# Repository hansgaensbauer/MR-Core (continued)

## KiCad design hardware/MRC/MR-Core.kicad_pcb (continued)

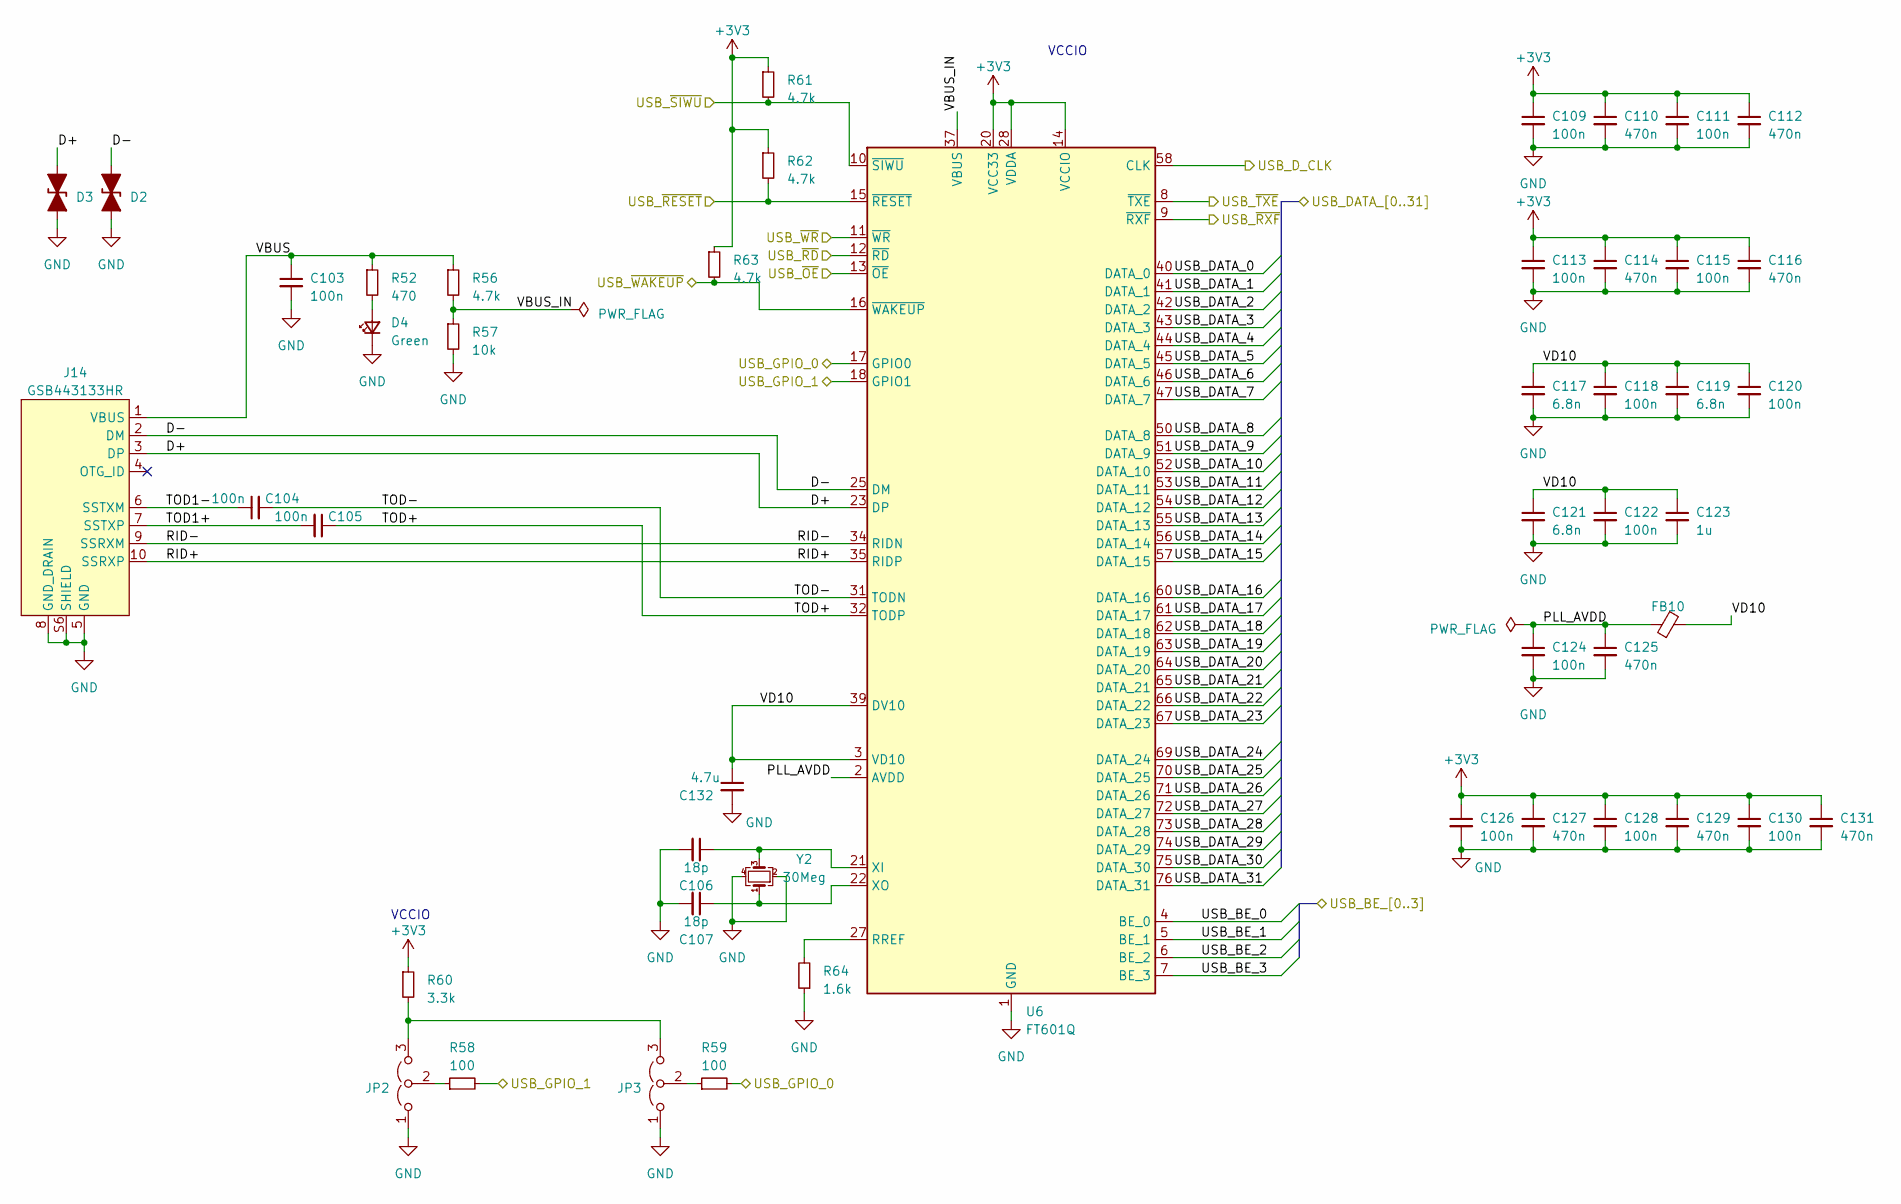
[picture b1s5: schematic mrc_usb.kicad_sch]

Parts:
C103, C104, C105, C109, C111, C113, C115, C118, C120, C122, C124, C126, C128, C130: 100n; C_0603_1608Metric; MPN C14663
C106, C107: 18p; C_0603_1608Metric; MPN C1647
C110, C112, C114, C116, C125, C127, C129, C131: 470n; C_0603_1608Metric; MPN C1623
C117, C119, C121: 6.8n; C_0603_1608Metric; MPN C1631
C123: 1u; C_0603_1608Metric; MPN C15849
C132: 4.7u; C_0603_1608Metric; MPN C19666
D2, D3: D_TVS_Filled; D_SOD-123
D4: Green; LED_0603_1608Metric; MPN C2290
FB10: FerriteBead_Small; L_0603_1608Metric; MPN C14709
J14: GSB443133HR; AMPHENOL_GSB443133HR; MPN C5428289(need to confirm)
JP2, JP3: Jumper_3_Open; SolderJumper-3_P1.3mm_Open_Pad1.0x1.5mm
R52: 470; R_0603_1608Metric; MPN C23179
R56, R61, R62, R63: 4.7k; R_0603_1608Metric; MPN C23162
R57: 10k; R_0603_1608Metric; MPN C25804
R58, R59: 100; R_0603_1608Metric; MPN C22775
R60: 3.3k; R_0603_1608Metric; MPN C22978
R64: 1.6k; R_0603_1608Metric; MPN C22847
U6: FT601Q; QFN-76-1EP_9x9mm_P0.4mm_EP5.81x6.31mm; MPN C1550513
Y2: 30Meg; Crystal_SMD_3225-4Pin_3.2x2.5mm; MPN C20885054

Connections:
+3V3: C109.1, C110.1, C111.1, C112.1, C113.1, C114.1, C115.1, C116.1, C126.1, C127.1, C128.1, C129.1, C130.1, C131.1, R60.1, R61.1, R62.1, R63.1, U6.14 (VCCIO), U6.20 (VCC33), U6.24 (VCC33), U6.28 (VDDA), U6.38 (VCC33), U6.49 (VCCIO), U6.59 (VCCIO), U6.68 (VCCIO); also elsewhere on the board
/Artix-7/USB_BE_0: U6.4 (BE_0); also elsewhere on the board
/Artix-7/USB_BE_1: U6.5 (BE_1); also elsewhere on the board
/Artix-7/USB_BE_2: U6.6 (BE_2); also elsewhere on the board
/Artix-7/USB_BE_3: U6.7 (BE_3); also elsewhere on the board
/Artix-7/USB_DATA_0: U6.40 (DATA_0); also elsewhere on the board
/Artix-7/USB_DATA_1: U6.41 (DATA_1); also elsewhere on the board
/Artix-7/USB_DATA_2: U6.42 (DATA_2); also elsewhere on the board
/Artix-7/USB_DATA_3: U6.43 (DATA_3); also elsewhere on the board
/Artix-7/USB_DATA_4: U6.44 (DATA_4); also elsewhere on the board
/Artix-7/USB_DATA_5: U6.45 (DATA_5); also elsewhere on the board
/Artix-7/USB_DATA_6: U6.46 (DATA_6); also elsewhere on the board
/Artix-7/USB_DATA_7: U6.47 (DATA_7); also elsewhere on the board
/Artix-7/USB_DATA_8: U6.50 (DATA_8); also elsewhere on the board
/Artix-7/USB_DATA_9: U6.51 (DATA_9); also elsewhere on the board
/Artix-7/USB_DATA_10: U6.52 (DATA_10); also elsewhere on the board
/Artix-7/USB_DATA_11: U6.53 (DATA_11); also elsewhere on the board
/Artix-7/USB_DATA_12: U6.54 (DATA_12); also elsewhere on the board
/Artix-7/USB_DATA_13: U6.55 (DATA_13); also elsewhere on the board
/Artix-7/USB_DATA_14: U6.56 (DATA_14); also elsewhere on the board
/Artix-7/USB_DATA_15: U6.57 (DATA_15); also elsewhere on the board
/Artix-7/USB_DATA_16: U6.60 (DATA_16); also elsewhere on the board
/Artix-7/USB_DATA_17: U6.61 (DATA_17); also elsewhere on the board
/Artix-7/USB_DATA_18: U6.62 (DATA_18); also elsewhere on the board
/Artix-7/USB_DATA_19: U6.63 (DATA_19); also elsewhere on the board
/Artix-7/USB_DATA_20: U6.64 (DATA_20); also elsewhere on the board
/Artix-7/USB_DATA_21: U6.65 (DATA_21); also elsewhere on the board
/Artix-7/USB_DATA_22: U6.66 (DATA_22); also elsewhere on the board
/Artix-7/USB_DATA_23: U6.67 (DATA_23); also elsewhere on the board
/Artix-7/USB_DATA_24: U6.69 (DATA_24); also elsewhere on the board
/Artix-7/USB_DATA_25: U6.70 (DATA_25); also elsewhere on the board
/Artix-7/USB_DATA_26: U6.71 (DATA_26); also elsewhere on the board
/Artix-7/USB_DATA_27: U6.72 (DATA_27); also elsewhere on the board
/Artix-7/USB_DATA_28: U6.73 (DATA_28); also elsewhere on the board
/Artix-7/USB_DATA_29: U6.74 (DATA_29); also elsewhere on the board
/Artix-7/USB_DATA_30: U6.75 (DATA_30); also elsewhere on the board
/Artix-7/USB_DATA_31: U6.76 (DATA_31); also elsewhere on the board
/Artix-7/USB_D_CLK: U6.58 (CLK); also elsewhere on the board
/Artix-7/USB_GPIO_0: R59.2, U6.17 (GPIO0); also elsewhere on the board
/Artix-7/USB_GPIO_1: R58.2, U6.18 (GPIO1); also elsewhere on the board
/Artix-7/USB_~OE: U6.13 (~OE); also elsewhere on the board
/Artix-7/USB_~RD: U6.12 (~RD); also elsewhere on the board
/Artix-7/USB_~RESET: R62.2, U6.15 (~RESET); also elsewhere on the board
/Artix-7/USB_~RXF: U6.9 (~RXF); also elsewhere on the board
/Artix-7/USB_~SIWU: R61.2, U6.10 (~SIWU); also elsewhere on the board
/Artix-7/USB_~TXE: U6.8 (~TXE); also elsewhere on the board
/Artix-7/USB_~WAKEUP: R63.2, U6.16 (~WAKEUP); also elsewhere on the board
/Artix-7/USB_~WR: U6.11 (~WR); also elsewhere on the board
/USB-FIFO/D+: D3.2 (A2), J14.3 (DP), U6.23 (DP)
/USB-FIFO/D-: D2.2 (A2), J14.2 (DM), U6.25 (DM)
/USB-FIFO/PLL_AVDD: C124.1, C125.1, FB10.1, U6.2 (AVDD)
/USB-FIFO/RID+: J14.10 (SSRXP), U6.35 (RIDP)
/USB-FIFO/RID-: J14.9 (SSRXM), U6.34 (RIDN)
/USB-FIFO/TOD1+: C105.2, J14.7 (SSTXP)
/USB-FIFO/TOD1-: C104.1, J14.6 (SSTXM)
/USB-FIFO/TOD+: C105.1, U6.32 (TODP)
/USB-FIFO/TOD-: C104.2, U6.31 (TODN)
/USB-FIFO/VBUS: C103.1, J14.1 (VBUS), R52.1, R56.1
/USB-FIFO/VBUS_IN: R56.2, R57.1, U6.37 (VBUS)
/USB-FIFO/VD10: C117.1, C118.1, C119.1, C120.1, C121.1, C122.1, C123.1, C132.1, FB10.2, U6.3 (VD10), U6.30 (VD10), U6.33 (VD10), U6.39 (DV10), U6.48 (VD10)
unnamed: D4.2 (A), R52.2
unnamed: JP2.3 (B), JP3.3 (B), R60.2
unnamed: JP2.2 (C), R58.1
unnamed: JP3.2 (C), R59.1
unnamed: R64.2, U6.27 (RREF)
unnamed: C106.1, U6.21 (XI), Y2.3
unnamed: C107.1, U6.22 (XO), Y2.1

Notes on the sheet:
VCCIO

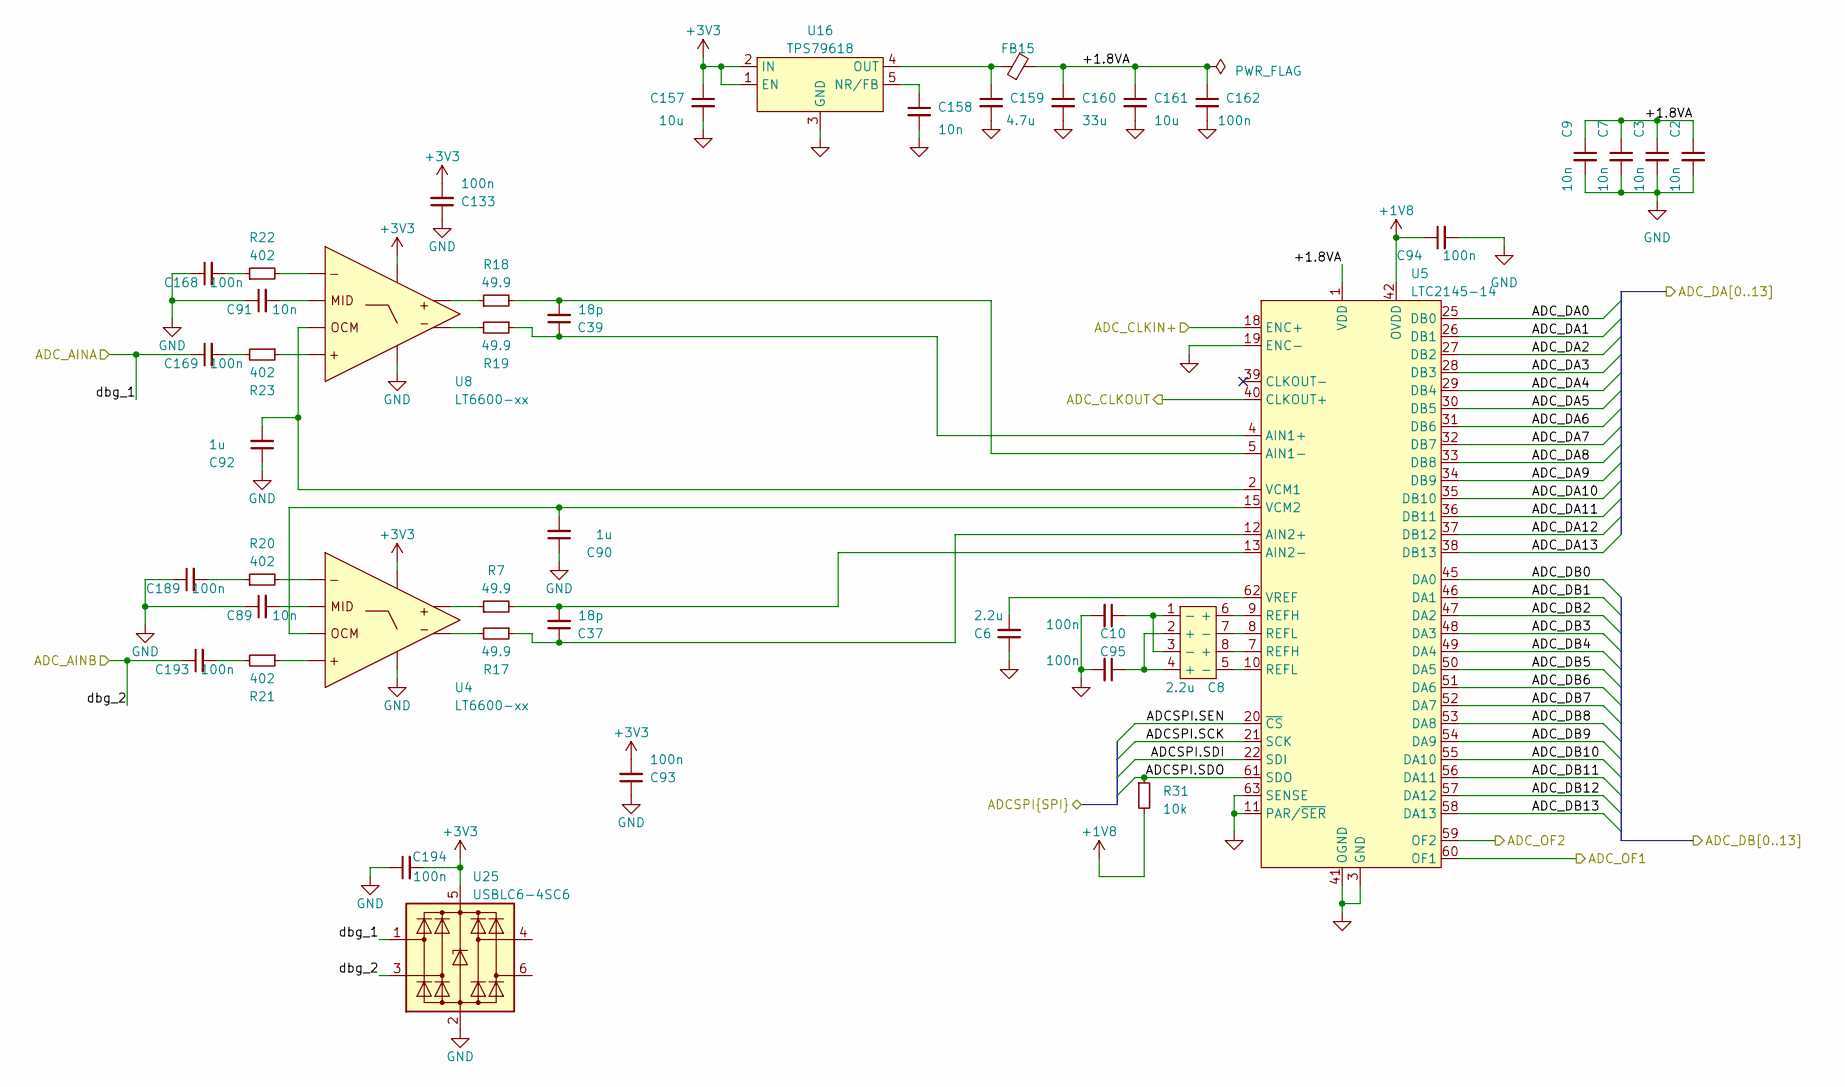
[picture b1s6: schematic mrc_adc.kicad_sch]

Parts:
C2, C3, C7, C9, C89, C91, C158: 10n; C_0603_1608Metric; MPN C57112
C6: 2.2u; C_0603_1608Metric; MPN C23630
C8: 2.2u; 0508_C_INTERDIGITATED; MPN C23630
C10, C93, C94, C95, C133, C162: 100n; C_0603_1608Metric; MPN C14663
C37, C39: 18p; C_0603_1608Metric; MPN C1647
C90, C92: 1u; C_0603_1608Metric; MPN C15849
C157, C161: 10u; C_0603_1608Metric; MPN C96446
C159: 4.7u; C_0603_1608Metric; MPN C19666
C160: 33u; C_0603_1608Metric; MPN C4978585
C168, C169, C189, C193, C194: 100n; C_0603_1608Metric; MPN C57112
FB15: FerriteBead_Small; L_0603_1608Metric; MPN C14709
R7, R17, R18, R19: 49.9; R_0603_1608Metric; MPN C23185
R20, R21, R22, R23: 402; R_0603_1608Metric; MPN C23049
R31: 10k; R_0603_1608Metric; MPN C25804
U4, U8: LT6600-xx; SO-8_3.9x4.9mm_P1.27mm; MPN C673220/C107980/C673198/C673202/C673216
U5: LTC2145-14; QFN-64-1EP_9x9mm_P0.5mm_EP7.15x7.15mm; MPN C679368/C679372
U16: TPS79618; SOT-223-6; MPN C2867020
U25: USBLC6-4SC6; SOT-23-6; MPN C5197386

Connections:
+1V8: C94.1, R31.2, U5.42 (OVDD); also elsewhere on the board
+3V3: C93.2, C133.2, C157.1, U4.3 (V+), U8.3 (V+), U16.1 (EN), U16.2 (IN); also elsewhere on the board
/ADC/+1.8VA: C2.1, C3.1, C7.1, C9.1, C160.1, C161.1, C162.1, FB15.2, U5.1 (VDD), U5.16 (VDD), U5.17 (VDD), U5.64 (VDD)
/ADC/ADCSPI.SCK: U5.21 (SCK); also elsewhere on the board
/ADC/ADCSPI.SDI: U5.22 (SDI); also elsewhere on the board
/ADC/ADCSPI.SDO: R31.1, U5.61 (SDO); also elsewhere on the board
/ADC/ADCSPI.SEN: U5.20 (~CS); also elsewhere on the board
/ADC/ADC_AINA: C169.2, R23.2; also elsewhere on the board
/ADC/ADC_AINB: C193.2, R21.2; also elsewhere on the board
/ADC/ADC_CLKOUT: U5.40 (CLKOUT+); also elsewhere on the board
/ADC/ADC_DA0: U5.25 (DB0); also elsewhere on the board
/ADC/ADC_DA1: U5.26 (DB1); also elsewhere on the board
/ADC/ADC_DA2: U5.27 (DB2); also elsewhere on the board
/ADC/ADC_DA3: U5.28 (DB3); also elsewhere on the board
/ADC/ADC_DA4: U5.29 (DB4); also elsewhere on the board
/ADC/ADC_DA5: U5.30 (DB5); also elsewhere on the board
/ADC/ADC_DA6: U5.31 (DB6); also elsewhere on the board
/ADC/ADC_DA7: U5.32 (DB7); also elsewhere on the board
/ADC/ADC_DA8: U5.33 (DB8); also elsewhere on the board
/ADC/ADC_DA9: U5.34 (DB9); also elsewhere on the board
/ADC/ADC_DA10: U5.35 (DB10); also elsewhere on the board
/ADC/ADC_DA11: U5.36 (DB11); also elsewhere on the board
/ADC/ADC_DA12: U5.37 (DB12); also elsewhere on the board
/ADC/ADC_DA13: U5.38 (DB13); also elsewhere on the board
/ADC/ADC_DB0: U5.45 (DA0); also elsewhere on the board
/ADC/ADC_DB1: U5.46 (DA1); also elsewhere on the board
/ADC/ADC_DB2: U5.47 (DA2); also elsewhere on the board
/ADC/ADC_DB3: U5.48 (DA3); also elsewhere on the board
/ADC/ADC_DB4: U5.49 (DA4); also elsewhere on the board
/ADC/ADC_DB5: U5.50 (DA5); also elsewhere on the board
/ADC/ADC_DB6: U5.51 (DA6); also elsewhere on the board
/ADC/ADC_DB7: U5.52 (DA7); also elsewhere on the board
/ADC/ADC_DB8: U5.53 (DA8); also elsewhere on the board
/ADC/ADC_DB9: U5.54 (DA9); also elsewhere on the board
/ADC/ADC_DB10: U5.55 (DA10); also elsewhere on the board
/ADC/ADC_DB11: U5.56 (DA11); also elsewhere on the board
/ADC/ADC_DB12: U5.57 (DA12); also elsewhere on the board
/ADC/ADC_DB13: U5.58 (DA13); also elsewhere on the board
/ADC/ADC_OF1: U5.60 (OF1); also elsewhere on the board
/ADC/ADC_OF2: U5.59 (OF2); also elsewhere on the board
/ADC_CLK+: U5.18 (ENC+); also elsewhere on the board
unnamed: C8.2 (+), C8.4 (+), C95.1
unnamed: C8.6 (+), U5.9 (REFH)
unnamed: C8.8 (+), U5.7 (REFH)
unnamed: C8.5 (-), U5.10 (REFL)
unnamed: C8.7 (-), U5.8 (REFL)
unnamed: C8.1 (-), C8.3 (-), C10.1
unnamed: C169.1, U25.1 (I/O1)
unnamed: C193.1, U25.3 (I/O2)
unnamed: R21.1, U4.8 (IN+)
unnamed: R20.2, U4.1 (IN-)
unnamed: R7.1, U4.4 (OUT+)
unnamed: R17.2, U4.5 (OUT-)
unnamed: C89.2, U4.7 (V_MID)
unnamed: C90.2, U4.2 (V_OCM), U5.15 (VCM2)
unnamed: C39.1, R19.1, U5.4 (AIN1+)
unnamed: C39.2, R18.2, U5.5 (AIN1-)
unnamed: C37.1, R17.1, U5.12 (AIN2+)
unnamed: C37.2, R7.2, U5.13 (AIN2-)
unnamed: C92.2, U5.2 (VCM1), U8.2 (V_OCM)
unnamed: C6.2, U5.62 (VREF)
unnamed: R23.1, U8.8 (IN+)
unnamed: R22.2, U8.1 (IN-)
unnamed: R18.1, U8.4 (OUT+)
unnamed: R19.2, U8.5 (OUT-)
unnamed: C91.2, U8.7 (V_MID)
unnamed: C158.1, U16.5 (NR/FB)
unnamed: C159.1, FB15.1, U16.4 (OUT)

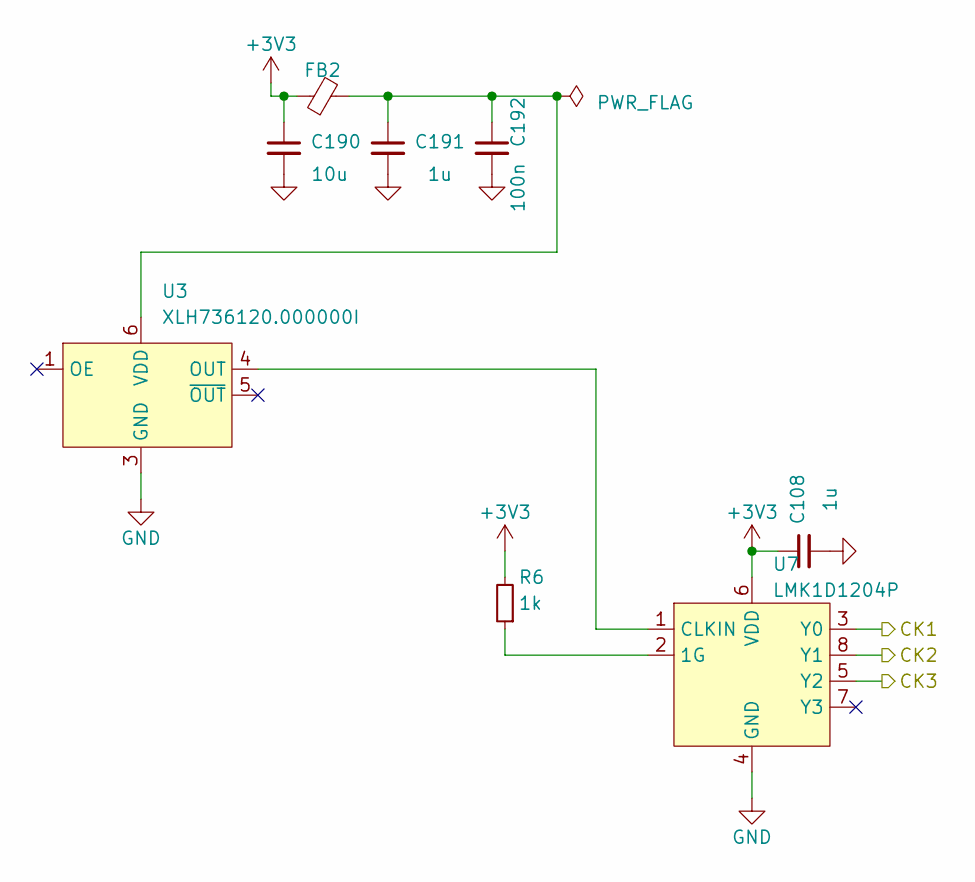
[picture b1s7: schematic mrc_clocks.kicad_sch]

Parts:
C108, C191: 1u; C_0603_1608Metric; MPN C15849
C190: 10u; C_0603_1608Metric; MPN C96446
C192: 100n; C_0603_1608Metric; MPN C14663
FB2: FerriteBead_Small; L_0603_1608Metric; MPN C14709
R6: 1k; R_0603_1608Metric; MPN C21190
U3: XLH736120.000000I; MPN C1670379
U7: LMK1D1204P; DFN-8_2x2mm_P0.5mm; MPN C3613664

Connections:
+3V3: C108.1, C190.1, FB2.1, R6.2, U7.6 (VDD); also elsewhere on the board
/ADC_CLK+: U7.3 (Y0); also elsewhere on the board
/DAC_CLK+: U7.8 (Y1); also elsewhere on the board
/FPGA_CLK+: U7.5 (Y2); also elsewhere on the board
unnamed: U3.4 (OUT), U7.1 (CLKIN)
unnamed: C191.1, C192.1, FB2.2, U3.6 (VDD)
unnamed: R6.1, U7.2 (1G)

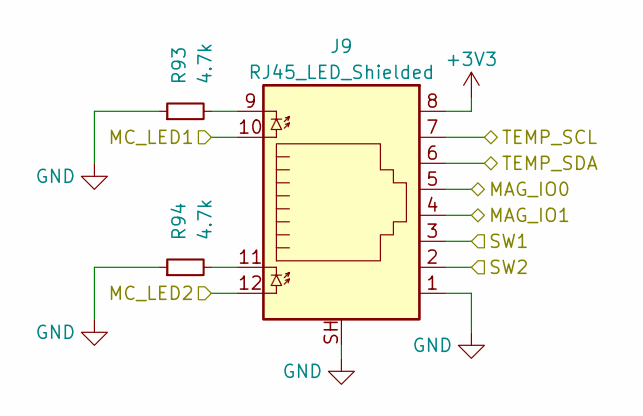
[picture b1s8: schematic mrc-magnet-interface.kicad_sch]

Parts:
J9: RJ45_LED_Shielded; RJ45_Amphenol_RJHSE538X; MPN C464586/C464587/C464588
R93, R94: 4.7k; R_0603_1608Metric; MPN C23162

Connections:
+3V3: J9.8; also elsewhere on the board
/Artix-7/SW1: J9.3; also elsewhere on the board
/Artix-7/SW2: J9.2; also elsewhere on the board
/Controller/MAG_IO0: J9.5; also elsewhere on the board
/Controller/MAG_IO1: J9.4; also elsewhere on the board
/Controller/MC_LED1: J9.10; also elsewhere on the board
/Controller/MC_LED2: J9.12; also elsewhere on the board
/Controller/TEMP_SCL: J9.7; also elsewhere on the board
/Controller/TEMP_SDA: J9.6; also elsewhere on the board
unnamed: J9.9, R93.2
unnamed: J9.11, R94.2

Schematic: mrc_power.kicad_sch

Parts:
C5, C134, C154, C197: 330n; C_0603_1608Metric; MPN C76621
C11: 4.7u; C_0603_1608Metric; MPN C19666
C135, C136, C199: 10u; C_0805_2012Metric; MPN C96446
C137, C155: 1u; C_0805_2012Metric; MPN C15849
C139, C198, C200: 47u; CP_Radial_D8.0mm_P3.50mm; MPN C318632
C170, C171: 220n; C_0603_1608Metric; MPN C21120
C201: 10u; C_1206_3216Metric; MPN C96446
D7: LED_Small; LED_0603_1608Metric; MPN C2286
J12: ASMPR45-1X2-RK; Powerpole_1x2; MPN C3683033
J19, J20, J21: Conn_01x02; JST_XH_B2B-XH-A_1x02_P2.50mm_Vertical
R1: 6.2k; R_0603_1608Metric; MPN C4260
R95: 5.62k; R_0603_1608Metric; MPN C23188
R96, R100: 3.3k; R_0603_1608Metric; MPN C22978
R97: 1k; R_0603_1608Metric; MPN C21190
R98: 2.2k; R_0603_1608Metric; MPN C4190
R99: 4.7k; R_0603_1608Metric; MPN C23162
R101: 10k; R_0603_1608Metric; MPN C25804
R102: 20k; R_0603_1608Metric; MPN C4184
TP7, TP8: TestPoint; TestPoint_THTPad_D2.0mm_Drill1.0mm
U14: LM7805_TO220; TO-220-3_BottomHeatsink; MPN C50931
U18: LM1085-12; TO-220-3_BottomHeatsink; MPN C130908
U19, U20: LD29300; P2PAK; MPN C500927
U21: MCP1827T-ADJ; P2PAK; MPN C632715(no stock)

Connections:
+1V0: C137.1, R99.1, U21.4 (OUT); also elsewhere on the board
+1V8: C136.1, R97.1, U20.4 (OUT); also elsewhere on the board
+3V3: C135.1, R95.1, U19.4 (OUT); also elsewhere on the board
+5V: C5.1, C11.1, C134.1, C139.1, C197.1, J21.1, R1.1, R101.2, R102.2, U14.3 (VO), U19.2 (IN), U20.2 (IN), U21.1 (INH), U21.2 (IN)
+12V: C198.1, C199.1, J20.1, U18.2 (VO)
+13V8: C154.1, C155.1, C200.1, C201.1, J12.1, J19.1, U14.1 (VI), U18.3 (VI); also elsewhere on the board
unnamed: D7.2 (A), R1.2
unnamed: R95.2, R96.1, U19.5 (ADJ)
unnamed: C171.2, R102.1, U19.1 (INH)
unnamed: R97.2, R98.1, U20.5 (ADJ)
unnamed: C170.2, R101.1, U20.1 (INH)
unnamed: R99.2, R100.1, U21.5 (ADJ)

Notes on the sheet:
Fan connector
LNA

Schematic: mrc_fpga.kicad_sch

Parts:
J6: Conn_02x05_Odd_Even; PinHeader_2x05_P2.54mm_Vertical
R27: 1k; R_0603_1608Metric; MPN C21190
U2: XC7A35T-FTG256; Xilinx_FTG256; MPN C9900024150

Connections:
+1V8: U2.A6 (VCCO_35), U2.B3 (VCCO_35), U2.D7 (VCCO_35), U2.E4 (VCCO_35), U2.F1 (VCCO_35), U2.J2 (VCCO_35); also elsewhere on the board
+3V3: J6.1, U2.A16 (VCCO_15), U2.B13 (VCCO_15), U2.C10 (VCCO_15), U2.E14 (VCCO_15), U2.H15 (VCCO_15), U2.J12 (VCCO_15), U2.L16 (VCCO_14), U2.M3 (VCCO_34), U2.M13 (VCCO_14), U2.N10 (VCCO_14), U2.P7 (VCCO_14), U2.R4 (VCCO_34), U2.R14 (VCCO_14), U2.T1 (VCCO_34), U2.T11 (VCCO_14); also elsewhere on the board
/ADC/ADC_CLKOUT: U2.F5 (IO_L13P_T2_MRCC_35); also elsewhere on the board
/ADC/ADC_DA0: U2.L3 (IO_L23P_T3_35); also elsewhere on the board
/ADC/ADC_DA1: U2.L2 (IO_L23N_T3_35); also elsewhere on the board
/ADC/ADC_DA2: U2.K2 (IO_L24N_T3_35); also elsewhere on the board
/ADC/ADC_DA3: U2.K3 (IO_L24P_T3_35); also elsewhere on the board
/ADC/ADC_DA4: U2.K1 (IO_L22P_T3_35); also elsewhere on the board
/ADC/ADC_DA5: U2.K5 (IO_25_35); also elsewhere on the board
/ADC/ADC_DA6: U2.J3 (IO_L21P_T3_DQS_35); also elsewhere on the board
/ADC/ADC_DA7: U2.J1 (IO_L22N_T3_35); also elsewhere on the board
/ADC/ADC_DA8: U2.J4 (IO_L19N_T3_VREF_35); also elsewhere on the board
/ADC/ADC_DA9: U2.H2 (IO_L20P_T3_35); also elsewhere on the board
/ADC/ADC_DA10: U2.J5 (IO_L19P_T3_35); also elsewhere on the board
/ADC/ADC_DA11: U2.H3 (IO_L21N_T3_DQS_35); also elsewhere on the board
/ADC/ADC_DA12: U2.G1 (IO_L17N_T2_35); also elsewhere on the board
/ADC/ADC_DA13: U2.G2 (IO_L17P_T2_35); also elsewhere on the board
/ADC/ADC_DB0: U2.H4 (IO_L18N_T2_35); also elsewhere on the board
/ADC/ADC_DB1: U2.F2 (IO_L15P_T2_DQS_35); also elsewhere on the board
/ADC/ADC_DB2: U2.E1 (IO_L15N_T2_DQS_35); also elsewhere on the board
/ADC/ADC_DB3: U2.F3 (IO_L14N_T2_SRCC_35); also elsewhere on the board
/ADC/ADC_DB4: U2.F4 (IO_L14P_T2_SRCC_35); also elsewhere on the board
/ADC/ADC_DB5: U2.D1 (IO_L10N_T1_AD15N_35); also elsewhere on the board
/ADC/ADC_DB6: U2.E2 (IO_L10P_T1_AD15P_35); also elsewhere on the board
/ADC/ADC_DB7: U2.E3 (IO_L11P_T1_SRCC_35); also elsewhere on the board
/ADC/ADC_DB8: U2.C1 (IO_L9P_T1_DQS_AD7P_35); also elsewhere on the board
/ADC/ADC_DB9: U2.D3 (IO_L11N_T1_SRCC_35); also elsewhere on the board
/ADC/ADC_DB10: U2.D4 (IO_L12P_T1_MRCC_35); also elsewhere on the board
/ADC/ADC_DB11: U2.B1 (IO_L9N_T1_DQS_AD7N_35); also elsewhere on the board
/ADC/ADC_DB12: U2.B2 (IO_L8P_T1_AD14P_35); also elsewhere on the board
/ADC/ADC_DB13: U2.A2 (IO_L8N_T1_AD14N_35); also elsewhere on the board
/Artix-7/DAC_DA0: U2.T7 (IO_L21P_T3_DQS_14); also elsewhere on the board
/Artix-7/DAC_DA1: U2.P8 (IO_L20P_T3_A08_D24_14); also elsewhere on the board
/Artix-7/DAC_DA2: U2.R8 (IO_L20N_T3_A07_D23_14); also elsewhere on the board
/Artix-7/DAC_DA3: U2.T8 (IO_L21N_T3_DQS_A06_D22_14); also elsewhere on the board
/Artix-7/DAC_DA4: U2.P9 (IO_L18N_T2_A11_D27_14); also elsewhere on the board
/Artix-7/DAC_DA5: U2.T9 (IO_L22P_T3_A05_D21_14); also elsewhere on the board
/Artix-7/DAC_DA6: U2.T10 (IO_L22N_T3_A04_D20_14); also elsewhere on the board
/Artix-7/DAC_DA7: U2.R10 (IO_L17P_T2_A14_D30_14); also elsewhere on the board
/Artix-7/DAC_DA8: U2.P10 (IO_L14P_T2_SRCC_14); also elsewhere on the board
/Artix-7/DAC_DA9: U2.R11 (IO_L17N_T2_A13_D29_14); also elsewhere on the board
/Artix-7/DAC_DA10: U2.P11 (IO_L14N_T2_SRCC_14); also elsewhere on the board
/Artix-7/DAC_DA11: U2.T12 (IO_L15N_T2_DQS_DOUT_CSO_B_14); also elsewhere on the board
/Artix-7/DAC_DA12: U2.R12 (IO_L15P_T2_DQS_RDWR_B_14); also elsewhere on the board
/Artix-7/DAC_DA13: U2.T13 (IO_L16N_T2_A15_D31_14); also elsewhere on the board
/Artix-7/DAC_DA14: U2.R13 (IO_L16P_T2_CSI_B_14); also elsewhere on the board
/Artix-7/DAC_DA15: U2.T14 (IO_L10P_T1_D14_14); also elsewhere on the board
/Artix-7/DAC_DB0: U2.R7 (IO_L24N_T3_A00_D16_14); also elsewhere on the board
/Artix-7/DAC_DB1: U2.R6 (IO_L24P_T3_A01_D17_14); also elsewhere on the board
/Artix-7/DAC_DB2: U2.P6 (IO_25_14); also elsewhere on the board
/Artix-7/DAC_DB3: U2.T5 (IO_L23N_T3_A02_D18_14); also elsewhere on the board
/Artix-7/DAC_DB4: U2.R5 (IO_L23P_T3_A03_D19_14); also elsewhere on the board
/Artix-7/DAC_DB5: U2.P5 (IO_L10P_T1_34); also elsewhere on the board
/Artix-7/DAC_DB6: U2.T4 (IO_L9P_T1_DQS_34); also elsewhere on the board
/Artix-7/DAC_DB7: U2.P4 (IO_L5P_T0_34); also elsewhere on the board
/Artix-7/DAC_DB8: U2.R3 (IO_L8P_T1_34); also elsewhere on the board
/Artix-7/DAC_DB9: U2.T3 (IO_L9N_T1_DQS_34); also elsewhere on the board
/Artix-7/DAC_DB10: U2.N4 (IO_L6N_T0_VREF_34); also elsewhere on the board
/Artix-7/DAC_DB11: U2.P3 (IO_L5N_T0_34); also elsewhere on the board
/Artix-7/DAC_DB12: U2.T2 (IO_L8N_T1_34); also elsewhere on the board
/Artix-7/DAC_DB13: U2.R2 (IO_L7P_T1_34); also elsewhere on the board
/Artix-7/DAC_DB14: U2.R1 (IO_L7N_T1_34); also elsewhere on the board
/Artix-7/DAC_DB15: U2.N3 (IO_L3P_T0_DQS_34); also elsewhere on the board
/Artix-7/DAC_PHSTR: U2.D8 (IO_L6P_T0_15); also elsewhere on the board
/Artix-7/FMC_ALE: U2.A14 (IO_L7N_T1_AD2N_15); also elsewhere on the board
/Artix-7/FMC_CLE: U2.C13 (IO_L12N_T1_MRCC_15); also elsewhere on the board
/Artix-7/FMC_~CE: U2.B12 (IO_L5P_T0_AD9P_15); also elsewhere on the board
/Artix-7/FMC_~OE: U2.B11 (IO_L4N_T0_15); also elsewhere on the board
/Artix-7/FMC_~WE: U2.C11 (IO_L11P_T1_SRCC_15); also elsewhere on the board
/Artix-7/FPGASPI.SCK: U2.M2 (IO_L2P_T0_34); also elsewhere on the board
/Artix-7/FPGASPI.SDI: U2.L4 (IO_L1P_T0_34); also elsewhere on the board
/Artix-7/FPGASPI.SEN: U2.L5 (IO_0_34); also elsewhere on the board
/Artix-7/FSMC_D0: U2.B14 (IO_L8N_T1_AD10N_15); also elsewhere on the board
/Artix-7/FSMC_D1: U2.C14 (IO_L8P_T1_AD10P_15); also elsewhere on the board
/Artix-7/FSMC_D2: U2.A12 (IO_L5N_T0_AD9N_15); also elsewhere on the board
/Artix-7/FSMC_D3: U2.C12 (IO_L11N_T1_SRCC_15); also elsewhere on the board
/Artix-7/FSMC_D4: U2.C8 (IO_L1P_T0_AD0P_15); also elsewhere on the board
/Artix-7/FSMC_D5: U2.A8 (IO_L2P_T0_AD8P_15); also elsewhere on the board
/Artix-7/FSMC_D6: U2.C9 (IO_L1N_T0_AD0N_15); also elsewhere on the board
/Artix-7/FSMC_D7: U2.D9 (IO_L6N_T0_VREF_15); also elsewhere on the board
/Artix-7/FSMC_D8: U2.A9 (IO_L2N_T0_AD8N_15); also elsewhere on the board
/Artix-7/FSMC_D9: U2.B9 (IO_L3P_T0_DQS_AD1P_15); also elsewhere on the board
/Artix-7/FSMC_D10: U2.B10 (IO_L4P_T0_15); also elsewhere on the board
/Artix-7/FSMC_D11: U2.A10 (IO_L3N_T0_DQS_AD1N_15); also elsewhere on the board
/Artix-7/FSMC_D12: U2.E12 (IO_L13P_T2_MRCC_15); also elsewhere on the board
/Artix-7/FSMC_D13: U2.D13 (IO_L12P_T1_MRCC_15); also elsewhere on the board
/Artix-7/FSMC_D14: U2.A13 (IO_L7P_T1_AD2P_15); also elsewhere on the board
/Artix-7/FSMC_D15: U2.E13 (IO_L13N_T2_MRCC_15); also elsewhere on the board
/Artix-7/GRINX_1: U2.A7 (IO_L1N_T0_AD4N_35); also elsewhere on the board
/Artix-7/GRINX_2: U2.B6 (IO_L2P_T0_AD12P_35); also elsewhere on the board
/Artix-7/GRINY_1: U2.B5 (IO_L2N_T0_AD12N_35); also elsewhere on the board
/Artix-7/GRINY_2: U2.A5 (IO_L3P_T0_DQS_AD5P_35); also elsewhere on the board
/Artix-7/GRINZ_1: U2.A4 (IO_L3N_T0_DQS_AD5N_35); also elsewhere on the board
/Artix-7/GRINZ_2: U2.B4 (IO_L4P_T0_35); also elsewhere on the board
/Artix-7/IO0: J6.3, U2.B7 (IO_L1P_T0_AD4P_35)
/Artix-7/IO1: J6.5, U2.H5 (IO_L18P_T2_35)
/Artix-7/IO2: J6.7, U2.N9 (IO_L18P_T2_A12_D28_14)
/Artix-7/IO3: J6.9, U2.M4 (IO_L1N_T0_34)
/Artix-7/IO4: J6.2, U2.M6 (IO_L19P_T3_A10_D26_14)
/Artix-7/IO5: J6.4, U2.M5 (IO_L6P_T0_34)
/Artix-7/IO6: J6.6, U2.E6 (IO_0_35)
/Artix-7/QSPI_D0: U2.J13 (IO_L1P_T0_D00_MOSI_14); also elsewhere on the board
/Artix-7/QSPI_D1: U2.J14 (IO_L1N_T0_D01_DIN_14); also elsewhere on the board
/Artix-7/QSPI_D2: U2.K15 (IO_L2P_T0_D02_14); also elsewhere on the board
/Artix-7/QSPI_D3: U2.K16 (IO_L2N_T0_D03_14); also elsewhere on the board
/Artix-7/QSPI_~CS: U2.L12 (IO_L6P_T0_FCS_B_14); also elsewhere on the board
/Artix-7/SW1: U2.G4 (IO_L16N_T2_35); also elsewhere on the board
/Artix-7/SW2: U2.H1 (IO_L20N_T3_35); also elsewhere on the board
/Artix-7/USB_BE_0: U2.M12 (IO_L6N_T0_D08_VREF_14); also elsewhere on the board
/Artix-7/USB_BE_1: U2.N12 (IO_L13N_T2_MRCC_14); also elsewhere on the board
/Artix-7/USB_BE_2: U2.K12 (IO_0_14); also elsewhere on the board
/Artix-7/USB_BE_3: U2.M15 (IO_L3N_T0_DQS_EMCCLK_14); also elsewhere on the board
/Artix-7/USB_DATA_0: U2.A15 (IO_L9N_T1_DQS_AD3N_15); also elsewhere on the board
/Artix-7/USB_DATA_1: U2.B16 (IO_L10N_T1_AD11N_15); also elsewhere on the board
/Artix-7/USB_DATA_2: U2.B15 (IO_L9P_T1_DQS_AD3P_15); also elsewhere on the board
/Artix-7/USB_DATA_3: U2.C16 (IO_L10P_T1_AD11P_15); also elsewhere on the board
/Artix-7/USB_DATA_4: U2.D14 (IO_L15P_T2_DQS_15); also elsewhere on the board
/Artix-7/USB_DATA_5: U2.D15 (IO_L15N_T2_DQS_ADV_B_15); also elsewhere on the board
/Artix-7/USB_DATA_6: U2.D16 (IO_L17N_T2_A25_15); also elsewhere on the board
/Artix-7/USB_DATA_7: U2.E15 (IO_L18N_T2_A23_15); also elsewhere on the board
/Artix-7/USB_DATA_8: U2.E16 (IO_L17P_T2_A26_15); also elsewhere on the board
/Artix-7/USB_DATA_9: U2.F14 (IO_L21N_T3_DQS_A18_15); also elsewhere on the board
/Artix-7/USB_DATA_10: U2.F15 (IO_L18P_T2_A24_15); also elsewhere on the board
/Artix-7/USB_DATA_11: U2.G14 (IO_L21P_T3_DQS_15); also elsewhere on the board
/Artix-7/USB_DATA_12: U2.G16 (IO_L22N_T3_A16_15); also elsewhere on the board
/Artix-7/USB_DATA_13: U2.G15 (IO_L24N_T3_RS0_15); also elsewhere on the board
/Artix-7/USB_DATA_14: U2.H14 (IO_L24P_T3_RS1_15); also elsewhere on the board
/Artix-7/USB_DATA_15: U2.H16 (IO_L22P_T3_A17_15); also elsewhere on the board
/Artix-7/USB_DATA_16: U2.G12 (IO_L19N_T3_A21_VREF_15); also elsewhere on the board
/Artix-7/USB_DATA_17: U2.H13 (IO_L20N_T3_A19_15); also elsewhere on the board
/Artix-7/USB_DATA_18: U2.J16 (IO_L23N_T3_FWE_B_15); also elsewhere on the board
/Artix-7/USB_DATA_19: U2.J15 (IO_L23P_T3_FOE_B_15); also elsewhere on the board
/Artix-7/USB_DATA_20: U2.K13 (IO_L5P_T0_D06_14); also elsewhere on the board
/Artix-7/USB_DATA_21: U2.L14 (IO_L4P_T0_D04_14); also elsewhere on the board
/Artix-7/USB_DATA_22: U2.L13 (IO_L5N_T0_D07_14); also elsewhere on the board
/Artix-7/USB_DATA_23: U2.M14 (IO_L4N_T0_D05_14); also elsewhere on the board
/Artix-7/USB_DATA_24: U2.M16 (IO_L7P_T1_D09_14); also elsewhere on the board
/Artix-7/USB_DATA_25: U2.N13 (IO_L11P_T1_SRCC_14); also elsewhere on the board
/Artix-7/USB_DATA_26: U2.N16 (IO_L7N_T1_D10_14); also elsewhere on the board
/Artix-7/USB_DATA_27: U2.P15 (IO_L8P_T1_D11_14); also elsewhere on the board
/Artix-7/USB_DATA_28: U2.P16 (IO_L8N_T1_D12_14); also elsewhere on the board
/Artix-7/USB_DATA_29: U2.R15 (IO_L9P_T1_DQS_14); also elsewhere on the board
/Artix-7/USB_DATA_30: U2.R16 (IO_L9N_T1_DQS_D13_14); also elsewhere on the board
/Artix-7/USB_DATA_31: U2.T15 (IO_L10N_T1_D15_14); also elsewhere on the board
/Artix-7/USB_D_CLK: U2.N11 (IO_L13P_T2_MRCC_14); also elsewhere on the board
/Artix-7/USB_GPIO_0: U2.D10 (IO_0_15); also elsewhere on the board
/Artix-7/USB_GPIO_1: U2.D11 (IO_L14N_T2_SRCC_15); also elsewhere on the board
/Artix-7/USB_~OE: U2.G11 (IO_25_15); also elsewhere on the board
/Artix-7/USB_~RD: U2.F13 (IO_L16N_T2_A27_15); also elsewhere on the board
/Artix-7/USB_~RESET: U2.E11 (IO_L14P_T2_SRCC_15); also elsewhere on the board
/Artix-7/USB_~RXF: U2.P13 (IO_L11N_T1_SRCC_14); also elsewhere on the board
/Artix-7/USB_~SIWU: U2.N6 (IO_L19N_T3_A09_D25_VREF_14); also elsewhere on the board
/Artix-7/USB_~TXE: U2.H12 (IO_L20P_T3_A20_15); also elsewhere on the board
/Artix-7/USB_~WAKEUP: U2.H11 (IO_L19P_T3_A22_15); also elsewhere on the board
/Artix-7/USB_~WR: U2.F12 (IO_L16P_T2_A28_15); also elsewhere on the board
/FPGA_CLK+: U2.N14 (IO_L12P_T1_MRCC_14); also elsewhere on the board
unnamed: R27.1, U2.L15 (IO_L3P_T0_DQS_PUDC_B_14)

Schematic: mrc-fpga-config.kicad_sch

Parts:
C18, C19, C20, C26, C30, C31, C35, C38, C87, C88, C150, C175, C176, C177, C181, C182, C183, C184, C185: 470n; C_0603_1608Metric; MPN C1623
C21, C22, C32, C33, C36, C40, C41, C172, C173, C178, C179, C186, C187: 4.7u; C_0603_1608Metric; MPN C19666
C25, C34, C42, C180, C188: 100u; C_0603_1608Metric; MPN C6663208
C174: 47u; C_0603_1608Metric; MPN C318632
D8, D9: LED_Small; LED_0603_1608Metric; MPN C2286
FB4: FerriteBead_Small; L_0603_1608Metric; MPN C14709
J13: Conn_02x07_Odd_Even; 0878321420
JP8: SolderJumper_3_Bridged12; SolderJumper-3_P1.3mm_Bridged2Bar12_Pad1.0x1.5mm
JP9: Jumper_2_Bridged; SolderJumper-2_P1.3mm_Bridged2Bar_Pad1.0x1.5mm
R2, R5, R51, R53, R54, R76, R81: 4.7k; R_0603_1608Metric; MPN C23162
R47: 330; R_0603_1608Metric; MPN C23138
R77, R78, R79, R80: 100; R_0603_1608Metric; MPN C22775
U2: XC7A35T-FTG256; Xilinx_FTG256; MPN C9900024150
U15: IS25LP256D-RMLE-TR; SOIC-16W_7.5x10.3mm_P1.27mm; MPN C2063380

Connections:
+1V0: C35.1, C36.1, C175.1, C176.1, C177.1, C178.1, C179.1, C180.1, U2.E10 (VCCBRAM), U2.F7 (VCCINT), U2.F9 (VCCINT), U2.F11 (VCCBRAM), U2.G6 (VCCINT), U2.H9 (VCCINT), U2.J6 (VCCINT), U2.K9 (VCCINT), U2.L8 (VCCINT); also elsewhere on the board
+1V8: C18.1, C19.1, C20.1, C32.1, C33.1, C34.1, C87.1, C88.1, C150.1, C172.1, C173.1, C174.1, U2.G8 (VCCADC_0), U2.G10 (VCCAUX), U2.J10 (VCCAUX), U2.K11 (VCCAUX), U2.L10 (VCCAUX); also elsewhere on the board
+3V3: C21.1, C22.1, C25.1, C26.1, C30.1, C31.1, C38.1, C40.1, C41.1, C42.1, C181.1, C182.1, C183.1, C184.1, C185.1, C186.1, C187.1, C188.1, J13.2, JP8.3 (B), R2.2, R47.1, R51.1, R53.2, R54.2, R76.1, R81.2, U2.E7 (CFGBVS_0), U2.L6 (VCCO_0), U2.M9 (M0_0), U15.2 (VCC); also elsewhere on the board
/Artix-7/FPGA Config/DONE: D9.2 (A), R47.2, U2.H10 (DONE_0)
/Artix-7/FPGA Config/FPGA_AGND: FB4.1, U2.G7 (GNDADC_0), U2.H7 (VREFN_0), U2.J8 (VREFP_0)
/Artix-7/FPGA Config/QSPI_SCK: U2.E8 (CCLK_0), U15.16 (SCK)
/Artix-7/FPGA Config/TCK: J13.6, U2.L7 (TCK_0)
/Artix-7/FPGA Config/TDI: J13.10, U2.N7 (TDI_0)
/Artix-7/FPGA Config/TDO: J13.8, U2.N8 (TDO_0)
/Artix-7/FPGA Config/TMS: J13.4, U2.M7 (TMS_0)
/Artix-7/FPGA Config/~INIT: D8.1 (K), JP9.2 (B), R51.2, U2.K10 (INIT_B_0)
/Artix-7/FPGA Config/~PROGRAM: R76.2, U2.L9 (PROGRAM_B_0)
/Artix-7/QSPI_D0: R77.1; also elsewhere on the board
/Artix-7/QSPI_D1: R78.1; also elsewhere on the board
/Artix-7/QSPI_D2: R80.1; also elsewhere on the board
/Artix-7/QSPI_D3: R79.1; also elsewhere on the board
/Artix-7/QSPI_~CS: R81.1, U15.7 (~CE); also elsewhere on the board
unnamed: D8.2 (A), R2.1
unnamed: D9.1 (K), R5.1
unnamed: JP8.2 (C), U2.M11 (M2_0)
unnamed: JP9.1 (A), U15.3 (~RESET/NC)
unnamed: R77.2, U15.15 (SI/IO0)
unnamed: R78.2, U15.8 (SO/IO1)
unnamed: R54.1, R79.2, U15.1 (~HOLD/IO3)
unnamed: R53.1, R80.2, U15.9 (~WP/IO2)

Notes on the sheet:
CHECK VCCADC
BANK 3
VCCBRAM
BANK 2
VCCAUX
BANK 4
BANK 1
VCCINT

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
